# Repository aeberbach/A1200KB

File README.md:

# A1200KB Mechanical keyboard for Amiga A1200

As of right now this is revision 4. I know it could be improved very, very slightly by changing the position of key groups by less than a millimetre but I think it's complete now. 

This PCB design was reverse-engineered from the original keyboard in an Amiga 1200. It is designed to connect to your Amiga 1200 with no modifications to the original machine, just take out the original keyboard and store it away safely. If you want an A600 keyboard, see my other repositories.

The A1200.net case (with internal PSU and partially-completed [ReAmiga](http://www.reamiga.info/) board)

The original Amiga case (with CF disk system and transparent floppy cover)

## Requirements
To make a working keyboard for your Amiga 1200, you need:

- one PCB (this project)
- 96 pieces MX-compatible PCB-mount (5-pin) keyswitch
- one LED (caps lock)
- one FFC connector, 32-way RA 1.25mm pitch. Molex 52044-3245 is one example, available from Mouser Electronics.
- one FFC ribbon cable, 32-way, 1.25mm pitch. Molex 15168-0400 is one example, available from Mouser Electronics.
- keycaps
- some way to mount the keyboard inside the Amiga (3D print some brackets from the STL folder...)
 
## Design
The Amiga 1200 keyboard is a simple passive key matrix connected via a 31-conductor cable. Some special keys are not on the matrix but have a dedicated circuit, such as the CTRL and Amiga keys - this is why so many conductors are necessary. The original Amiga 1200 PCB uses a 31-way FFC connector, I was not able to buy this anywhere as they are long discontinued. However cutting one conductor away from the cable allows it to fit in the Amiga connector with 31 conductors and to the keyboard with 32 conductors and everything is fine. The specified FFC cable is slightly longer than required but in 2019 there is not  a lot of choice available, so the longer one will do. 
I had my boards made with 1.6mm PCB substrate as any other thickness gets disproportionally expensive, no other special options. Using a piece of aluminium rail, 10x3mm, will make it as stiff as a keyboard should be while maintaining enough space underneath for an accelerator or Indivision etc. This is supported either side by the 3D printed mounts. Cover the aluminium with some kapton or other insulation if you have other internal components that may come dangerously close but in a stock Amiga there is plenty of clearance.

### Amiga Keycaps
These aren't widely available. I've tried making some using a blank set of keycaps from aliexpress and a laser etcher, but I do not know of anywhere that sells a MX-stem set of Amiga keycaps. I am using a 9U space bar but you can just as easily use 7U. If gaps either side of the space bother you, 3D print something to fill the space.

If you want a perfect set of keys, visit pimpmykeyboard.com - it will not be cheap but if you look hard enough you will find every key, even the Amiga keys, and you can have any legend printed on any size keycap so it is possible to make a perfect set. It will not be cheap. You can se a partial sample in the A1200.net picture. I am currently waiting for the extra numpad keys to arrive to complete this keyboard.

## Construction
Without going into all the detail here - as there is lots of detail on www.grayunicorn.com - I rate this a mid-level project. There is no power, no delicate soldering, and nothing can really be inserted the wrong way. Mounting the keyboard requires 3D printing the files you will find in the 3Dfiles folder.

If you have a replacement case produced by A1200.net then pick that folder, else the other folder. I don't know about cases made by ESCOM but I don't think they are at all different from the Commodore cases. I printed these in PETG, 0.4mm nozzle, 0.2mm layer height, supports are necessary. Mounting the keyboard with these designs allows the use of an accelerator card with a thick SIMM; I may design alternates if I get a slimmer accelerator, bringing the keys further back into the case but there is not much room.
 
You can damage your Amiga if you don't know what you are doing. Please be careful and if you are not experienced in projects like this get some help, maybe vist your local makerspace, and don't hurt yourself or your computer.

## Share
Most of all - if you have any suggestions for improvements, adding an issue or a pull request to this repo would be much appreciated. And share your project with the Amiga community, I'd really like to see what you made.

#### Donate?
I hate to think what this has cost so far. It's been fun and I'd do it again, but if you'd like to help the next project happen that would be awesome.

Note this this project is licensed under CC BY-NC-SA 4.0 - only noncommercial use is permitted! (By all means sell the excess PCBs you get, at cost, if you order some for your own use)

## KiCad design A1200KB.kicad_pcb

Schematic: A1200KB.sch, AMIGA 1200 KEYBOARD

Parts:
J1: Conn_01x32_Female; FFC-1.25mm-RA-5204403245
K1: ESC; MXOnly-1U-NoLED
K2: F1; MXOnly-1.25U-NoLED
K3: F2; MXOnly-1.25U-NoLED
K4: F3; MXOnly-1.25U-NoLED
K5: F4; MXOnly-1.25U-NoLED
K6: F5; MXOnly-1.25U-NoLED
K7: F6; MXOnly-1.25U-NoLED
K8: F7; MXOnly-1.25U-NoLED
K9: F8; MXOnly-1.25U-NoLED
K10: F9; MXOnly-1.25U-NoLED
K11: F10; MXOnly-1.25U-NoLED
K12: TILDE; MXOnly-1.5U-NoLED
K13: 1; MXOnly-1U-NoLED
K14: 2; MXOnly-1U-NoLED
K15: 3; MXOnly-1U-NoLED
K16: 4; MXOnly-1U-NoLED
K17: 5; MXOnly-1U-NoLED
K18: 6; MXOnly-1U-NoLED
K19: 7; MXOnly-1U-NoLED
K20: 8; MXOnly-1U-NoLED
K21: 9; MXOnly-1U-NoLED
K22: 0; MXOnly-1U-NoLED
K23: MINUS; MXOnly-1U-NoLED
K24: PLUS; MXOnly-1U-NoLED
K25: PIPE; MXOnly-1U-NoLED
K26: BS; MXOnly-1U-NoLED
K27: DEL; MXOnly-1.5U-NoLED
K28: HELP; MXOnly-1.5U-NoLED
K29: NUM_(; MXOnly-1U-NoLED
K30: NUM_); MXOnly-1U-NoLED
K31: NUM_DIV; MXOnly-1U-NoLED
K32: NUM_MULT; MXOnly-1U-NoLED
K33: TAB; MXOnly-2U-NoLED
K34: Q; MXOnly-1U-NoLED
K35: W; MXOnly-1U-NoLED
K36: E; MXOnly-1U-NoLED
K37: R; MXOnly-1U-NoLED
K38: T; MXOnly-1U-NoLED
K39: Y; MXOnly-1U-NoLED
K40: U; MXOnly-1U-NoLED
K41: I; MXOnly-1U-NoLED
K42: O; MXOnly-1U-NoLED
K43: P; MXOnly-1U-NoLED
K44: L.CURLY; MXOnly-1U-NoLED
K45: R.CURLY; MXOnly-1U-NoLED
K46: RETURN; MXOnly-ISO
K47: NUM_7; MXOnly-1U-NoLED
K48: NUM_8; MXOnly-1U-NoLED
K49: NUM_9; MXOnly-1U-NoLED
K50: NUM_MINUS; MXOnly-1U-NoLED
K51: CTRL; MXOnly-1.25U-NoLED
K52: CAPSLOCK; MXOnly-1U
K53: A; MXOnly-1U-NoLED
K54: S; MXOnly-1U-NoLED
K55: D; MXOnly-1U-NoLED
K56: F; MXOnly-1U-NoLED
K57: G; MXOnly-1U-NoLED
K58: H; MXOnly-1U-NoLED
K59: J; MXOnly-1U-NoLED
K60: K; MXOnly-1U-NoLED
K61: L; MXOnly-1U-NoLED
K62: COLON; MXOnly-1U-NoLED
K63: \"; MXOnly-1U-NoLED
K64: R.BLANK; MXOnly-1U-NoLED
K65: UP; MXOnly-1U-NoLED
K66: NUM_4; MXOnly-1U-NoLED
K67: NUM_5; MXOnly-1U-NoLED
K68: NUM_6; MXOnly-1U-NoLED
K69: NUM_PLUS; MXOnly-1U-NoLED
K70: L.SHIFT; MXOnly-1.75U-NoLED
K71: L.BLANK; MXOnly-1U-NoLED
K72: Z; MXOnly-1U-NoLED
K73: X; MXOnly-1U-NoLED
K74: C; MXOnly-1U-NoLED
K75: V; MXOnly-1U-NoLED
K76: B; MXOnly-1U-NoLED
K77: N; MXOnly-1U-NoLED
K78: M; MXOnly-1U-NoLED
K79: R.CROC; MXOnly-1U-NoLED
K80: L.CROC; MXOnly-1U-NoLED
K81: QUESTION; MXOnly-1U-NoLED
K82: R.SHIFT; MXOnly-2.75U-NoLED
K83: LEFT; MXOnly-1U-NoLED
K84: DOWN; MXOnly-1U-NoLED
K85: RIGHT; MXOnly-1U-NoLED
K86: NUM_1; MXOnly-1U-NoLED
K87: NUM_2; MXOnly-1U-NoLED
K88: NUM_3; MXOnly-1U-NoLED
K89: NUM_ENTER; MXOnly-2U-NoLED
K90: L.ALT; MXOnly-1.25U-NoLED
K91: L.AMIGA; MXOnly-1.25U-NoLED
K92: SPACE; MXOnly-7U-NoLED
K93: R.AMIGA; MXOnly-1.25U-NoLED
K94: R.ALT; MXOnly-1.25U-NoLED
K95: NUM_0; MXOnly-2U-NoLED
K96: NUM_DECIMAL; MXOnly-1U-NoLED

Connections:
/1: J1.1, K33.1, K34.2, K35.2, K36.2, K37.2, K38.2, K39.1, K40.2, K41.2, K42.2, K43.2, K44.2, K45.2, K46.1, K83.2
/2: J1.2, K27.2, K52.2, K53.2, K54.2, K55.2, K56.2, K57.2, K58.1, K59.2, K60.2, K61.2, K62.2, K63.2, K64.2, K85.2
/3: J1.3, K26.2, K71.2, K72.2, K73.2, K74.2, K75.2, K76.2, K77.1, K78.2, K79.2, K80.2, K81.2, K84.1, K92.2
/4: J1.4, K32.2, K47.2, K48.2, K49.2, K50.2, K66.2, K67.2, K68.2, K69.2, K86.2, K87.2, K88.2, K89.2, K95.1, K96.2
/5: J1.5, K12.2, K13.2, K14.2, K15.2, K16.2, K17.2, K18.1, K19.2, K20.1, K21.2, K22.2, K23.2, K24.2, K25.1, K65.1
/6: J1.6, K82.1
/7: J1.7, K1.2, K2.2, K3.2, K4.2, K5.2, K6.2, K7.1, K8.2, K9.2, K10.2, K11.2, K28.2, K29.2, K30.2, K31.2
/8: J1.8, K94.1
/9: J1.9, K52.3
/10: J1.10, K93.2
/11: J1.11, K51.2
/12: J1.12, K70.2
/13: J1.13, K90.2
/14: J1.14, K91.2
/15: J1.15, K1.1, K12.1, K32.1, K33.2, K52.1, K71.1
/16: J1.16, K13.1, K29.1, K34.1, K53.1, K69.1, K72.1
/17: J1.17, K2.1, K14.1, K35.1, K49.1, K54.1, K73.1
/18: J1.18, K3.1, K15.1, K36.1, K55.1, K68.1, K74.1
/19: J1.19, K4.1, K16.1, K37.1, K56.1, K75.1, K88.1
/20: J1.20, K5.1, K17.1, K38.1, K57.1, K76.1, K96.1
/21: J1.21, K6.1, K18.2, K39.2, K48.1, K58.2, K77.2
/22: J1.22, K19.1, K30.1, K40.1, K59.1, K67.1, K78.1
/23: J1.23, K7.2, K20.2, K41.1, K60.1, K79.1, K87.1
/24: J1.24, K21.1, K31.1, K42.1, K61.1, K80.1, K89.1
/25: J1.25, K8.1, K22.1, K43.1, K47.1, K62.1, K81.1
/26: J1.26, K9.1, K23.1, K44.1, K63.1, K66.1
/27: J1.27, K10.1, K24.1, K45.1, K64.1, K86.1, K92.1
/28: J1.28, K11.1, K25.2, K26.1, K27.1, K46.2, K95.2
/29: J1.29, K28.1, K50.1, K65.2, K83.1, K84.2, K85.1
/30: J1.30, K51.1, K70.1, K82.2, K90.1, K91.1, K93.1, K94.2
/31: J1.31, K52.4

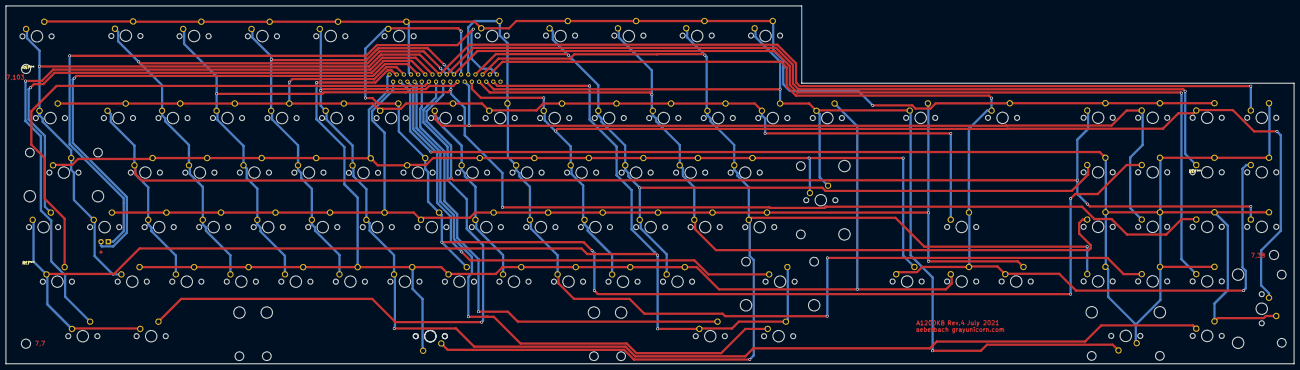
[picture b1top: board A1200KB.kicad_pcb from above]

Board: 2 copper layers, 450.0 x 125.0 mm, 97 parts (1 on the bottom side), 31 nets.

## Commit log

2019-03-19 The new PCB
2019-03-20 Placed all
2019-03-20 Datasheets
2019-03-21 Layout complete and art to ourpcb
2019-04-13 Routed again, cutout for LED PCB, sized for Al supports
2019-04-14 Submitted R2 to ourpcb
2019-05-13 MIT License
2019-05-16 added image
2019-05-16 readme file
2019-05-16 add pcb image
2019-05-16 warning for rev 1
2019-05-16 Printer note
2019-05-16 typo
2019-07-18 STL files, readme revised
2019-10-03 Removed stray holes from return key area
    Removed stray holes from return key area as shown here: https://i.imgur.com/tEPMIs2.png
    Would have caused exposed lines.
2019-10-21 fixed bad route at return key
2019-10-21 Renegerated mfg outputs
2019-12-11 Rev 3!
    Board is smaller for more flexibility in mounting. Stabs are turned inwards. Traces moved to make fitting mounting holes easier. This will need a new 3D printed mounting solution…
2020-01-02 A link that will open an A1200 layout
    keyboard-layout-editor.com
2020-02-12 Updated for rev 3.
2020-02-12 Replace rev 2 3D support STL with rev 3
2020-05-30 New 3D printed files for A1200.net case
2020-05-30 fix keyboard link
2020-05-30 Fixed base support files
2021-07-22 Begin rev4, organize 3D files
2021-08-18 Better alignment of key groups with each other
    More or less a perfect fit now. Also new mount STLs for A1200.net case. I'm getting around to redoing the Commodore case mounts soon.
2021-08-29 Rev 4 complete
2021-08-29 fix images?
2021-08-29 Fix captions
2021-08-29 ReAmiga link, revise text
2024-06-19 CC-BY-NC-SA
2024-06-19 Use A1200
2024-06-30 Open with KiCAD 8
2024-10-06 last revision
